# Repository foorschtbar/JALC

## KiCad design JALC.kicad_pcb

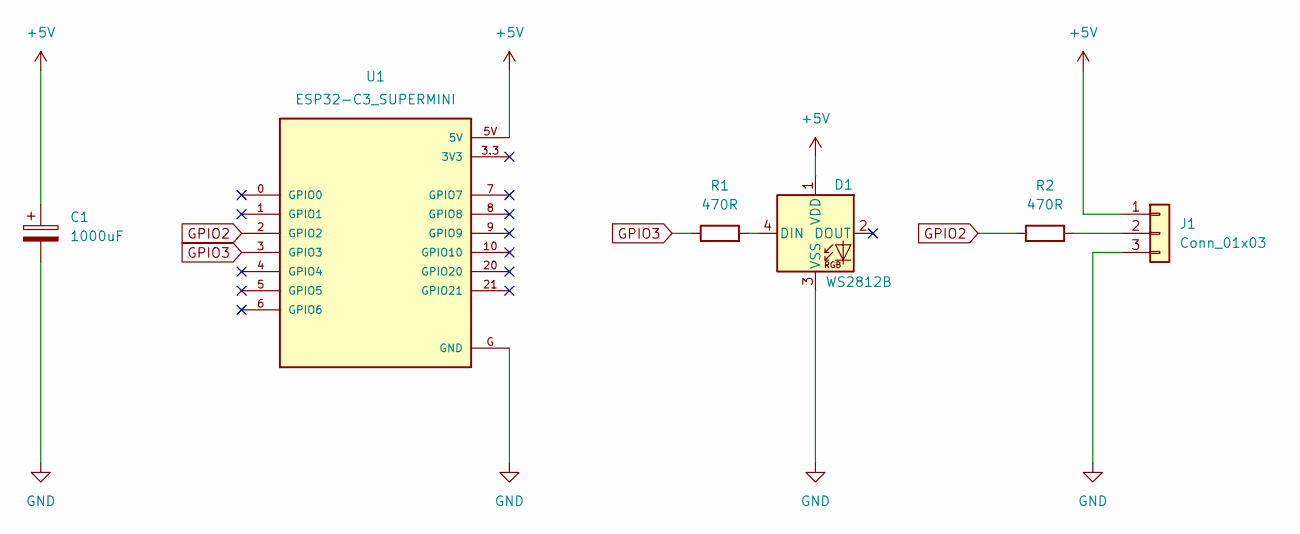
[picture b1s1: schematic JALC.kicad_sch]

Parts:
C1: 1000uF; CP_EIA-7343-43_Kemet-X
D1: WS2812B; LED_WS2812B_PLCC4_5.0x5.0mm_P3.2mm
J1: Conn_01x03; SolderConnector
R1, R2: 470R; R_0805_2012Metric_Pad1.20x1.40mm_HandSolder
U1: ESP32-C3_SUPERMINI; MODULE_ESP32-C3_SUPERMINI

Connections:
+5V: C1.1, D1.1 (VDD), J1.1, U1.5V
GND: C1.2, D1.3 (VSS), J1.3, U1.G (GND)
GPIO2: R2.1, U1.2 (GPIO2)
GPIO3: R1.1, U1.3 (GPIO3)
unnamed: D1.4 (DIN), R1.2
unnamed: J1.2, R2.2

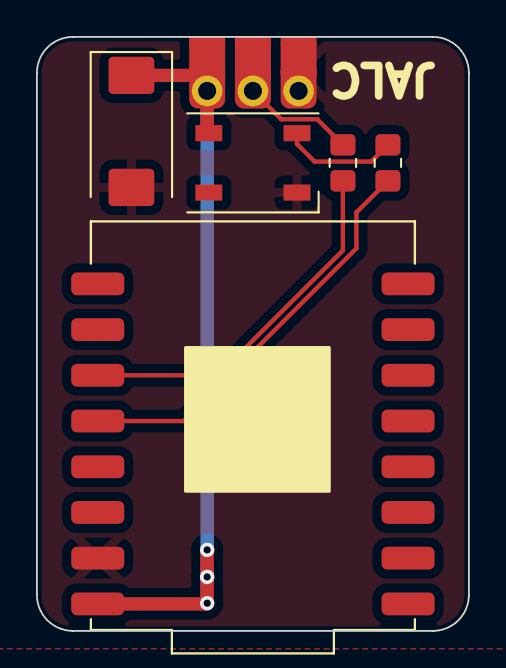
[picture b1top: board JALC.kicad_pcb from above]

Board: 2 copper layers, 24.0 x 33.0 mm, 6 parts (0 on the bottom side), 6 nets.

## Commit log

2024-09-25 REV1.0
2024-10-05 Added REV2.0 (ESP32-C3)
